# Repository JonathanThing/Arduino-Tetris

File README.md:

# Arduino-Tetris
Tetris on an Arduino Mega

Video Demo: <br />

This was my Gr.12 Computer Engineering Final project where I designed, created, and programmed Tetris from start to finish.

Software Used:
- KiCAD
- Arduino IDE

Stage 1: Design
- Using KiCad, I created a circuit diagram and PCB layout

Stage 2: Assembly
- I soldered the components onto the PCB, 

Stage 3: Programming
- I programmed Tetris and the music player

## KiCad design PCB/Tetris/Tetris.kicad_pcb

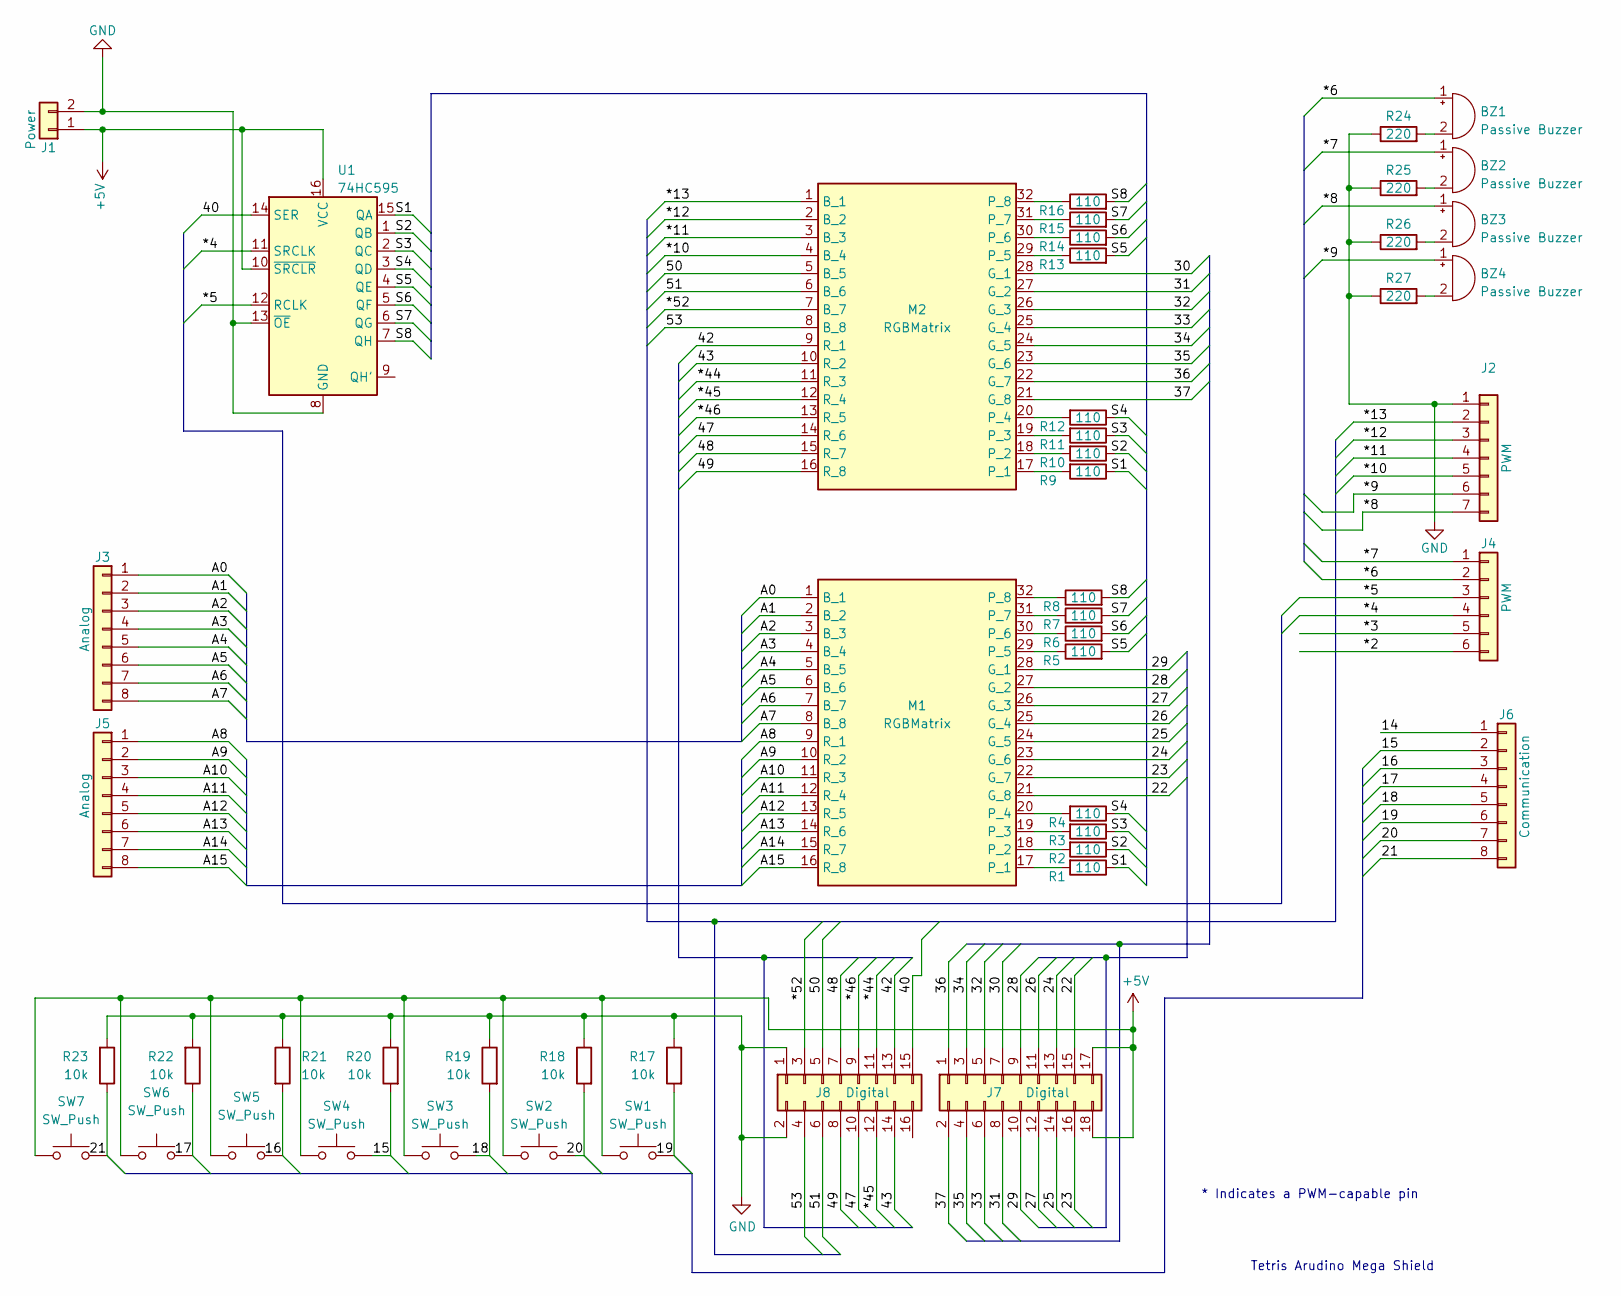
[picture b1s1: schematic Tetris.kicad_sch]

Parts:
BZ1, BZ2, BZ3, BZ4: Passive Buzzer; Buzzer_TDK_PS1240P02BT_D12.2mm_H6.5mm
J1: Power; PinHeader_1x02_P2.54mm_Vertical
J2: PWM; PinHeader_1x07_P2.54mm_Vertical
J3, J5: Analog; PinHeader_1x08_P2.54mm_Vertical
J4: PWM; PinHeader_1x06_P2.54mm_Vertical
J6: Communication; PinHeader_1x08_P2.54mm_Vertical
J7: Digital; PinHeader_2x09_P2.54mm_Vertical
J8: Digital; PinHeader_2x08_P2.54mm_Vertical
M1, M2: RGBMatrix
R1, R2, R3, R4, R5, R6, R7, R8, R9, R10, R11, R12: 110; R_Axial_DIN0207_L6.3mm_D2.5mm_P12.40mm_Horizontal
R13, R14, R15, R16: 110; R_Axial_DIN0207_L6.3mm_D2.5mm_P10.16mm_Horizontal
R17, R18: 10k; R_Axial_DIN0207_L6.3mm_D2.5mm_P7.62mm_Horizontal
R19, R20, R21, R22, R23: 10k; R_Axial_DIN0207_L6.3mm_D2.5mm_P10.16mm_Horizontal
R24, R25, R26, R27: 220; R_Axial_DIN0207_L6.3mm_D2.5mm_P12.40mm_Horizontal
SW1, SW2, SW3, SW4, SW5, SW6, SW7: SW_Push; SW_PUSH_6mm_H4.3mm
U1: 74HC595; DIP-16_W7.62mm_Socket_LongPads

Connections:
+5V: J1.1, J7.17, J7.18, SW1.2, SW2.2, SW3.2, SW4.2, SW5.2, SW6.2, SW7.2, U1.10 (~SRCLR), U1.16 (VCC)
/14: J6.1
/15: J6.2, R20.2, SW4.1
/16: J6.3, R21.2, SW5.1
/17: J6.4, R22.1, SW6.1
/18: J6.5, R19.2, SW3.1
/19: J6.6, R17.2, SW1.1
/20: J6.7, R18.2, SW2.1
/21: J6.8, R23.1, SW7.1
/22: J7.15, M1.21 (G_8)
/23: J7.16, M1.22 (G_7)
/24: J7.13, M1.23 (G_6)
/25: J7.14, M1.24 (G_5)
/26: J7.11, M1.25 (G_4)
/27: J7.12, M1.26 (G_3)
/28: J7.9, M1.27 (G_2)
/29: J7.10, M1.28 (G_1)
/30: J7.7, M2.28 (G_1)
/31: J7.8, M2.27 (G_2)
/32: J7.5, M2.26 (G_3)
/33: J7.6, M2.25 (G_4)
/34: J7.3, M2.24 (G_5)
/35: J7.4, M2.23 (G_6)
/36: J7.1, M2.22 (G_7)
/37: J7.2, M2.21 (G_8)
/40: J8.15, U1.14 (SER)
/41: J8.16
/42: J8.13, M2.9 (R_1)
/43: J8.14, M2.10 (R_2)
/47: J8.10, M2.14 (R_6)
/48: J8.7, M2.15 (R_7)
/49: J8.8, M2.16 (R_8)
/50: J8.5, M2.5 (B_5)
/51: J8.6, M2.6 (B_6)
/53: J8.4, M2.8 (B_8)
/*2: J4.6
/*3: J4.5
/*4: J4.4, U1.11 (SRCLK)
/*5: J4.3, U1.12 (RCLK)
/*6: BZ1.1 (-), J4.2
/*7: BZ2.1 (-), J4.1
/*8: BZ3.1 (-), J2.7
/*9: BZ4.1 (-), J2.6
/*10: J2.5, M2.4 (B_4)
/*11: J2.4, M2.3 (B_3)
/*12: J2.3, M2.2 (B_2)
/*13: J2.2, M2.1 (B_1)
/*44: J8.11, M2.11 (R_3)
/*45: J8.12, M2.12 (R_4)
/*46: J8.9, M2.13 (R_5)
/*52: J8.3, M2.7 (B_7)
/A0: J3.1, M1.1 (B_1)
/A1: J3.2, M1.2 (B_2)
/A2: J3.3, M1.3 (B_3)
/A3: J3.4, M1.4 (B_4)
/A4: J3.5, M1.5 (B_5)
/A5: J3.6, M1.6 (B_6)
/A6: J3.7, M1.7 (B_7)
/A7: J3.8, M1.8 (B_8)
/A8: J5.1, M1.9 (R_1)
/A9: J5.2, M1.10 (R_2)
/A10: J5.3, M1.11 (R_3)
/A11: J5.4, M1.12 (R_4)
/A12: J5.5, M1.13 (R_5)
/A13: J5.6, M1.14 (R_6)
/A14: J5.7, M1.15 (R_7)
/A15: J5.8, M1.16 (R_8)
/S1: R1.1, R9.1, U1.15 (QA)
/S2: R2.1, R10.1, U1.1 (QB)
/S3: R3.1, R11.1, U1.2 (QC)
/S4: R4.1, R12.1, U1.3 (QD)
/S5: R5.2, R13.2, U1.4 (QE)
/S6: R6.2, R14.2, U1.5 (QF)
/S7: R7.2, R15.2, U1.6 (QG)
/S8: R8.2, R16.2, U1.7 (QH)
GND: J1.2, J2.1, J8.1, J8.2, R17.1, R18.1, R19.1, R20.1, R21.1, R22.2, R23.2, R24.1, R25.1, R26.1, R27.1, U1.8 (GND), U1.13 (~OE)
unnamed: BZ1.2 (+), R24.2
unnamed: BZ2.2 (+), R25.2
unnamed: BZ3.2 (+), R26.2
unnamed: BZ4.2 (+), R27.2
unnamed: M1.17 (P_1), R1.2
unnamed: M1.18 (P_2), R2.2
unnamed: M1.19 (P_3), R3.2
unnamed: M1.20 (P_4), R4.2
unnamed: M1.29 (P_5), R5.1
unnamed: M1.30 (P_6), R6.1
unnamed: M1.31 (P_7), R7.1
unnamed: M1.32 (P_8), R8.1
unnamed: M2.17 (P_1), R9.2
unnamed: M2.18 (P_2), R10.2
unnamed: M2.19 (P_3), R11.2
unnamed: M2.20 (P_4), R12.2
unnamed: M2.29 (P_5), R13.1
unnamed: M2.30 (P_6), R14.1
unnamed: M2.31 (P_7), R15.1
unnamed: M2.32 (P_8), R16.1

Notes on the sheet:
* Indicates a PWM-capable pin
Tetris Arudino Mega Shield

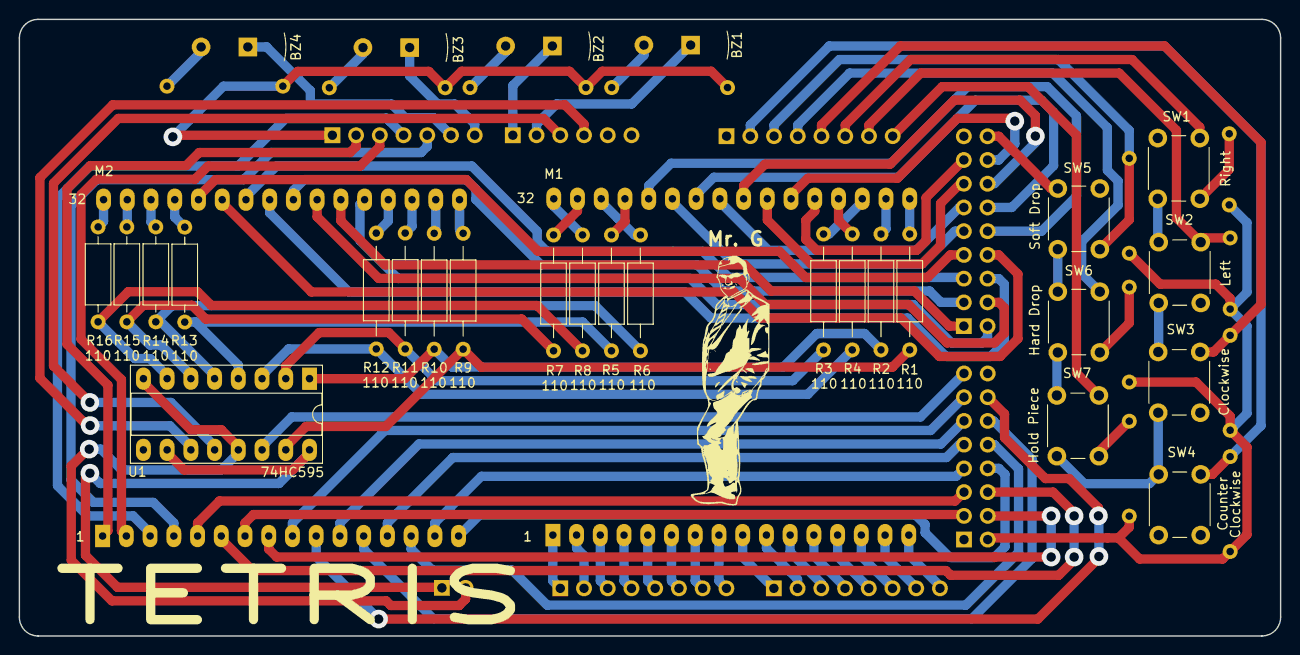
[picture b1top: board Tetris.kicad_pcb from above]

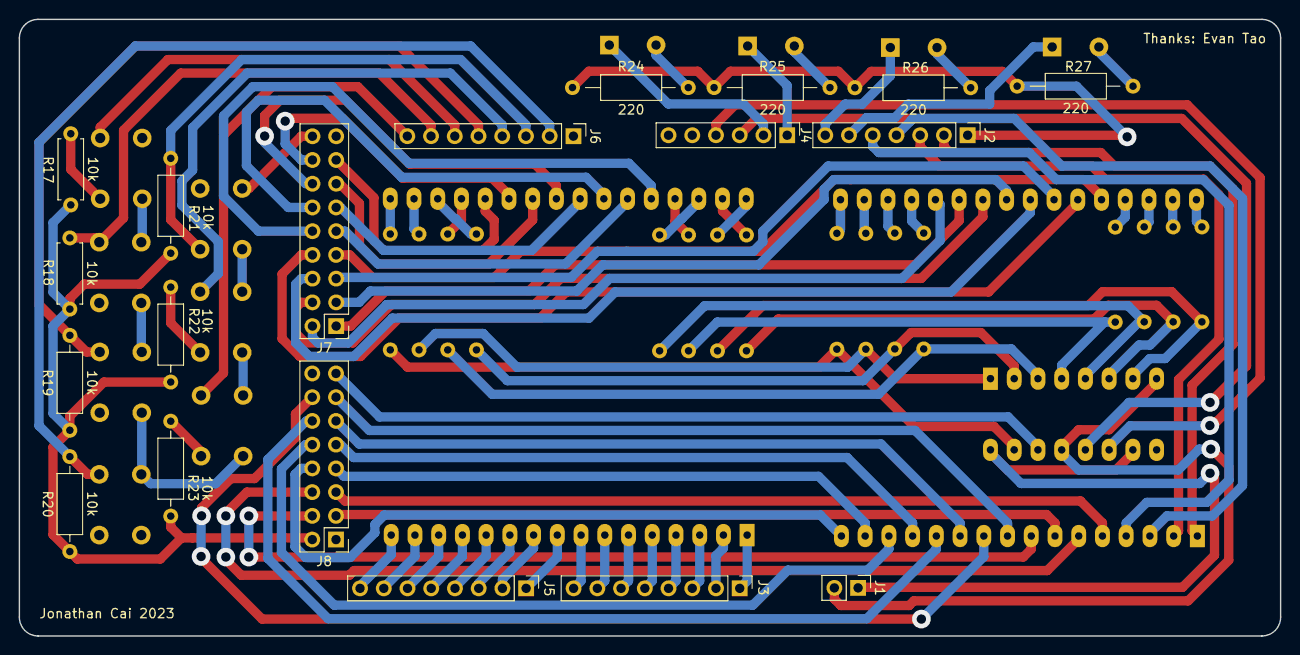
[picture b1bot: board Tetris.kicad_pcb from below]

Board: 2 copper layers, 135.0 x 66.0 mm, 51 parts (19 on the bottom side), 92 nets.

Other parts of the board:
G1, G2: LOGO

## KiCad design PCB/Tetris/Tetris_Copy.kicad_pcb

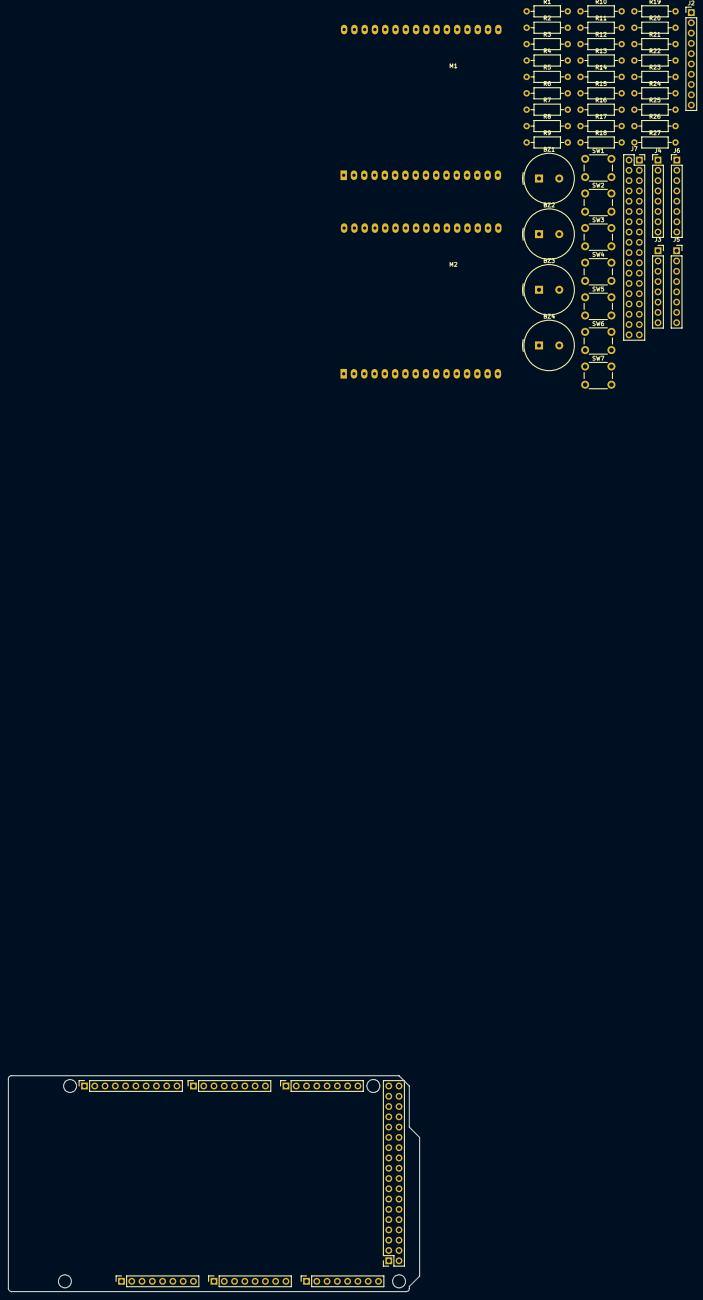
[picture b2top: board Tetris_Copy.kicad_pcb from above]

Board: 2 copper layers, 101.6 x 53.3 mm, 57 parts (0 on the bottom side), 110 nets, no tracks yet.

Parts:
BZ1, BZ2, BZ3, BZ4: Passive Buzzer; Buzzer_TDK_PS1240P02BT_D12.2mm_H6.5mm
J1: Power; PinSocket_1x08_P2.54mm_Vertical
J2: PWM; PinHeader_1x10_P2.54mm_Vertical
J2#2: PWM; PinSocket_1x10_P2.54mm_Vertical
J3, J3#2, J5, J5#2: Analog; PinSocket_1x08_P2.54mm_Vertical
J4: PWM; PinSocket_1x08_P2.54mm_Vertical
J4#2: PWM; PinHeader_1x08_P2.54mm_Vertical
J6: Communication; PinHeader_1x08_P2.54mm_Vertical
J6#2: Communication; PinSocket_1x08_P2.54mm_Vertical
J7, J7#2: Digital; PinSocket_2x18_P2.54mm_Vertical
M1, M2: RGBMatrix
MH1, MH2, MH5, MH6: MountingHole_3.2mm
R1, R2, R3, R4, R5, R6, R7, R8, R20, R21, R22, R23, R24, R25, R26, R27: 110; R_Axial_DIN0207_L6.3mm_D2.5mm_P10.16mm_Horizontal
R9, R10, R11, R12: 220; R_Axial_DIN0207_L6.3mm_D2.5mm_P10.16mm_Horizontal
R13, R14, R15, R16, R17, R18, R19: 10k; R_Axial_DIN0207_L6.3mm_D2.5mm_P10.16mm_Horizontal
SW1, SW2, SW3, SW4, SW5, SW6, SW7: SW_Push; SW_PUSH_6mm_H4.3mm

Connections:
+5V: J1.5, J7.35, J7.36, J7#2.35, J7#2.36
/1: M1.1 (B_1), M2.1 (B_1)
/2: M1.2 (B_2), M2.2 (B_2)
/3: M1.3 (B_3), M2.3 (B_3)
/4: M1.4 (B_4), M2.4 (B_4)
/5: M1.5 (B_5), M2.5 (B_5)
/6: M1.6 (B_6), M2.6 (B_6)
/7: M1.7 (B_7), M2.7 (B_7)
/8: M1.8 (B_8), M2.8 (B_8)
/9: M1.9 (R_1), M2.9 (R_1)
/10: M1.10 (R_2), M2.10 (R_2)
/11: M1.11 (R_3), M2.11 (R_3)
/12: M1.12 (R_4), M2.12 (R_4)
/13: M1.13 (R_5), M2.13 (R_5)
/14: M1.14 (R_6), M2.14 (R_6)
/15: M1.15 (R_7), M2.15 (R_7)
/16: M1.16 (R_8), M2.16 (R_8)
/17: R1.1, R27.1
/18: R2.1, R26.1
/19: R3.1, R25.1
/20: R4.1, R24.1
/21: M1.21 (G_1), M2.21 (G_1)
/22: J7.33, J7#2.33, M1.22 (G_2), M2.22 (G_2)
/23: J7.34, J7#2.34, M1.23 (G_3), M2.23 (G_3)
/24: J7.31, J7#2.31, M1.24 (G_4), M2.24 (G_4)
/25: J7.32, J7#2.32, M1.25 (G_5), M2.25 (G_5)
/26: J7.29, J7#2.29, M1.26 (G_6), M2.26 (G_6)
/27: J7.30, J7#2.30, M1.27 (G_7), M2.27 (G_7)
/28: J7.27, J7#2.27, M1.28 (G_8), M2.28 (G_8)
/29: J7.28, J7#2.28, R5.1, R23.1
/30: J7.25, J7#2.25, R6.1, R22.1
/31: J7.26, J7#2.26, R7.1, R21.1
/32: J7.23, J7#2.23, R8.1, R20.1
/33: J7.24, J7#2.24
/34: J7.21, J7#2.21
/35: J7.22, J7#2.22
/36: J7.19, J7#2.19
/37: J7.20, J7#2.20
/38: J7.17, J7#2.17
/39: J7.18, J7#2.18
/40: J7.15, J7#2.15
/41: J7.16, J7#2.16
/42: J7.13, J7#2.13
/43: J7.14, J7#2.14
/47: J7.10, J7#2.10
/48: J7.7, J7#2.7
/49: J7.8, J7#2.8
/50: J7.5, J7#2.5
/51: J7.6, J7#2.6
/53: J7.4, J7#2.4
/*2: J4.6, J4#2.6
/*3: J4.5, J4#2.5
/*4: J4.4, J4#2.4
/*5: J4.3, J4#2.3
/*6: J4.2, J4#2.2
/*7: J4.1, J4#2.1
/*8: J2.10, J2#2.10
/*9: J2.9, J2#2.9
/*10: J2.8, J2#2.8
/*11: J2.7, J2#2.7
/*12: J2.6, J2#2.6
/*13: J2.5, J2#2.5
/*44: J7.11, J7#2.11
/*45: J7.12, J7#2.12
/*46: J7.9, J7#2.9
/*52: J7.3, J7#2.3
/A0: J3.1, J3#2.1
/A1: J3.2, J3#2.2
/A2: J3.3, J3#2.3
/A3: J3.4, J3#2.4
/A4: J3.5, J3#2.5
/A5: J3.6, J3#2.6
/A6: J3.7, J3#2.7
/A7: J3.8, J3#2.8
/A8: J5.1, J5#2.1
/A9: J5.2, J5#2.2
/A10: J5.3, J5#2.3
/A11: J5.4, J5#2.4
/A12: J5.5, J5#2.5
/A13: J5.6, J5#2.6
/A14: J5.7, J5#2.7
/A15: J5.8, J5#2.8
/AREF: J2.3, J2#2.3
/RX0/0: J4.8, J4#2.8
/RX1/19: J6.6, J6#2.6
/RX2/17: J6.4, J6#2.4
/RX3/15: J6.2, J6#2.2
/SCL/21: J2.1, J2#2.1, J6.8, J6#2.8
/SDA/20: J2.2, J2#2.2, J6.7, J6#2.7
/TX0/1: J4.7, J4#2.7
/TX1/18: J6.5, J6#2.5
/TX2/16: J6.3, J6#2.3
/TX3/14: J6.1, J6#2.1
GND: J1.6, J1.7, J2.4, J2#2.4, J7.1, J7.2, J7#2.1, J7#2.2
unnamed: M1.17 (P_1), R1.2
unnamed: M1.18 (P_2), R2.2
unnamed: M1.19 (P_3), R3.2
unnamed: M1.20 (P_4), R4.2
unnamed: M1.29 (P_5), R5.2
unnamed: M1.30 (P_6), R6.2
unnamed: M1.31 (P_7), R7.2
unnamed: M1.32 (P_8), R8.2
unnamed: M2.17 (P_1), R27.2
unnamed: M2.18 (P_2), R26.2
unnamed: M2.19 (P_3), R25.2
unnamed: M2.20 (P_4), R24.2
unnamed: M2.29 (P_5), R23.2
unnamed: M2.30 (P_6), R22.2
unnamed: M2.31 (P_7), R21.2
unnamed: M2.32 (P_8), R20.2

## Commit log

2023-05-02 Added Tetris Code
2023-05-02 Added PCB work to sync
2023-05-02 Successfuly Steal code (Fix later)
2023-05-02 something happened
2023-05-02 Schematics and sync
2023-05-03 Very little change
2023-05-03 Sync change
2023-05-04 sync
2023-05-05 Making diabolical progress
2023-05-06 Saving progress
2023-05-06 Finished PCB
    Finish PCB,
    will still have to double check it
2023-05-06 Added funnyjoke
2023-05-06 Sync changes
2023-05-08 very little progress very sad
2023-05-08 snyc
2023-05-10 Small Changes
2023-05-10 Crunch time
2023-05-10 sync hcnages
2023-05-11 MASSIVE PROGRESS
    Redesign PCB to use ports
2023-05-13 Synch Changes? Idk
2023-05-14 brain damage
    I run away for this today
2023-05-14 Lets go progress
    I made some prgoress
2023-05-15 Graphics Basicaly Works
2023-05-15 It just works
2023-05-17 A very bad implementation of OOP
2023-05-17 Small minor changes
2023-05-18 Can of worms
2023-05-20 Progress checkpoint
2023-05-20 Saving progress for rewrite
2023-05-21 Made very little progress
2023-05-21 implemented random generation
2023-05-23 Checkpoint
    Save code for rewrite
2023-05-23 sync random buggy code
2023-05-25 sync small changes
2023-06-07 Something change
2023-06-08 something progres sno goood
2023-06-09 catastrophic failure managmeent
2023-06-14 synz changes
2023-06-14 Diabolically failing
2023-06-14 Syncing changes
2023-06-14 added small functions saving progress
2023-06-15 Sync changes
    Implemented block collision etc
2023-06-16 Sync Progress
2023-06-17 Finished writing midi converter code
2023-06-18 Saving catastrophic changes
2023-06-18 Saving Progress before testing out risky code
2023-06-18 Finish integrating music with tetris
2023-06-18 Saving Progress for rewrite
    Going to implement interrupts. Not sure if saving this is wroth it since its literally just one line :skull
2023-06-19 Rewrite and tidy the code
2023-06-19 Removed borrowed code
2023-06-19 Small update
2023-07-19 Create README.md
    work in progress
2023-07-21 Cleaned up and tidy repository
    Removed duplicated/unwanted PCB files,
    Added pictures for read me
